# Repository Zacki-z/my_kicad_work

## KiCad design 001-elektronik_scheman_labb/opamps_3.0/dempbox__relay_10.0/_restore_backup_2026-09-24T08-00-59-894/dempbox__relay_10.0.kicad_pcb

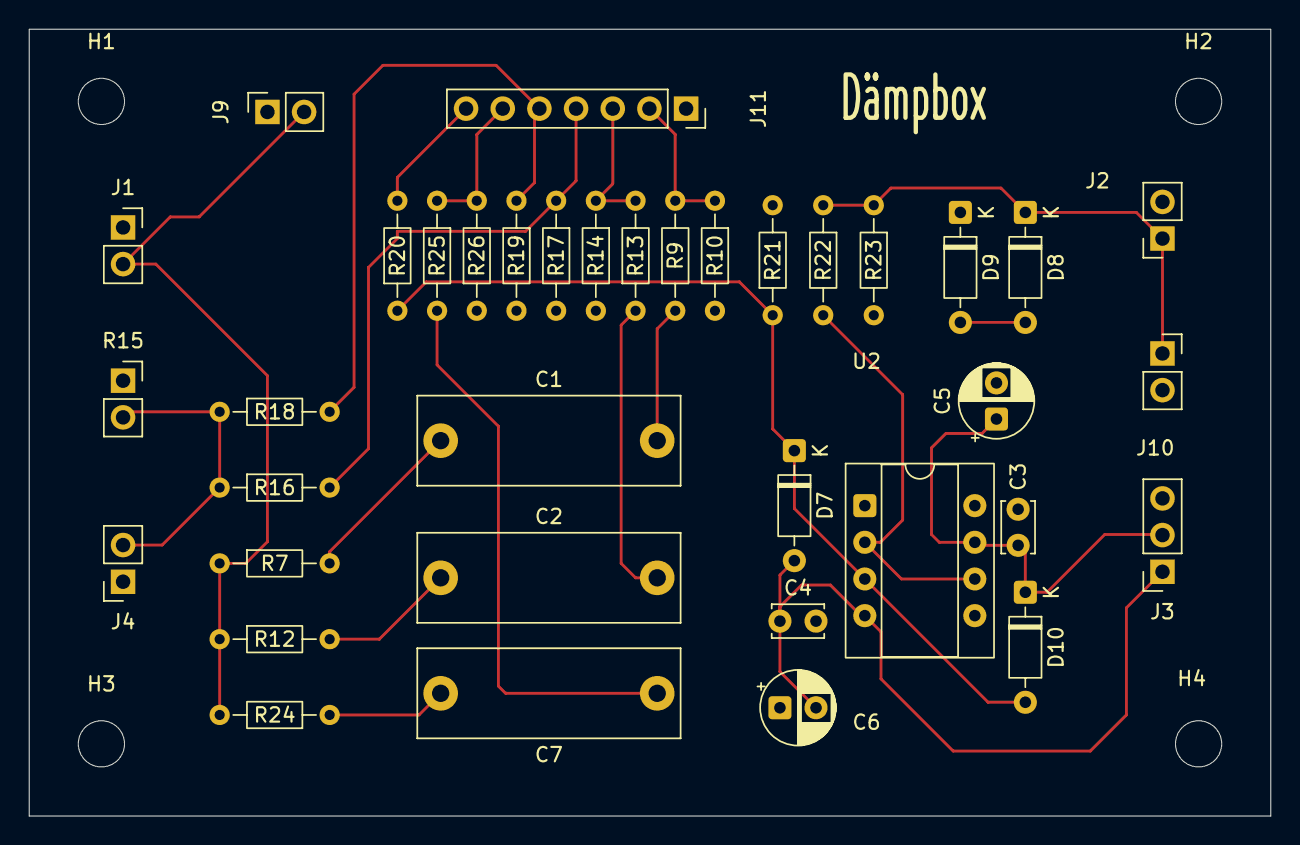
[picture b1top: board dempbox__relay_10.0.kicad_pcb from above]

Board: 2 copper layers, 86.0 x 54.5 mm, 41 parts (0 on the bottom side), 21 nets.

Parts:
C1, C2: 100 nF 630v; C_Rect_L18.0mm_W6.0mm_P15.00mm_FKS3_FKP3
C3, C4: 100 nF; C_Disc_D3.4mm_W2.1mm_P2.50mm
C5, C6: 10 uF; CP_Radial_D5.0mm_P2.50mm
C7: 100 nF 630V; C_Rect_L18.0mm_W6.0mm_P15.00mm_FKS3_FKP3
D7, D10: 1N4148; D_DO-35_SOD27_P7.62mm_Horizontal
D8, D9: BZX55C5V1; D_DO-35_SOD27_P7.62mm_Horizontal
H1, H2, H3, H4: MountingHole; MountingHole_3.2mm_M3
J1: Test_probe; PinSocket_1x02_P2.54mm_Vertical
J2: TO_Focusrite_input; PinSocket_1x02_P2.54mm_Vertical
J3: OP_AMP_PWR; PinSocket_1x03_P2.54mm_Vertical
J4: Speaker; PinSocket_1x02_P2.54mm_Vertical
J9, J10: Mätinstrument; PinSocket_1x02_P2.54mm_Vertical
J11: J_SW_SIGNAL; PinSocket_1x07_P2.54mm_Vertical
R7, R12, R21, R26: 1M; R_Axial_DIN0204_L3.6mm_D1.6mm_P7.62mm_Horizontal
R9, R13: 953k; R_Axial_DIN0204_L3.6mm_D1.6mm_P7.62mm_Horizontal
R10: 20K; R_Axial_DIN0204_L3.6mm_D1.6mm_P7.62mm_Horizontal
R14: 274k; R_Axial_DIN0204_L3.6mm_D1.6mm_P7.62mm_Horizontal
R15: 8 50W; PinSocket_1x02_P2.54mm_Vertical
R16, R23: 100k; R_Axial_DIN0204_L3.6mm_D1.6mm_P7.62mm_Horizontal
R17: 1k; R_Axial_DIN0204_L3.6mm_D1.6mm_P7.62mm_Horizontal
R18: 90,9k; R_Axial_DIN0204_L3.6mm_D1.6mm_P7.62mm_Horizontal
R19: 10k; R_Axial_DIN0204_L3.6mm_D1.6mm_P7.62mm_Horizontal
R20: 20k; R_Axial_DIN0204_L3.6mm_D1.6mm_P7.62mm_Horizontal
R22: 330R; R_Axial_DIN0204_L3.6mm_D1.6mm_P7.62mm_Horizontal
R24, R25: 10K; R_Axial_DIN0204_L3.6mm_D1.6mm_P7.62mm_Horizontal
U2: OPA134; CERDIP-8_W7.62mm_SideBrazed_Socket

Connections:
/INTPUT: J1.2, J9.2, R7.1, R12.1, R24.2
/INT_1_10: C2.1, R12.2
/INT_1_10_OUT: J11.3, R13.2, R14.1
/INT_1_100: C1.1, R7.2
/INT_1_100_OUT: J11.2, R9.2, R10.1
/LOW_1_1: C7.2, R24.1
/LOW_1_1_OUT: J11.6, R25.1, R26.2
/SPK_1_10_OUT: J11.5, R18.2, R19.1
/SPK_1_100: J4.2, R15.2, R16.1, R18.1
/SPK_1_100_OUT: J11.4, R16.2, R17.1
/sound-card/12V+: C3.1, C5.1, D10.1 (K), J3.2, U2.7 (V+)
/sound-card/12V-: C4.1, C6.2, D7.2 (A), J3.1, U2.4 (V-)
/sound-card/OP_AMP_OUT: R22.2, U2.2 (-), U2.6
/sound-card/audio_out: D8.1 (K), J2.1, J10.1, R22.1, R23.1
MEASURE_GND: C3.2, C4.2, C5.2, C6.1, D9.1 (K), J1.1, J2.2, J3.3, J4.1, J9.1, J10.2, R10.2, R14.2, R15.1, R17.2, R19.2, R21.2, R23.2, R26.1
MEASURE_SIGNAL: J11.7, R20.2
unnamed: C1.2, R9.1
unnamed: C2.2, R13.1
unnamed: C7.1, R25.2
unnamed: D8.2 (A), D9.2 (A)
unnamed: D7.1 (K), D10.2 (A), R20.1, R21.1, U2.3 (+)

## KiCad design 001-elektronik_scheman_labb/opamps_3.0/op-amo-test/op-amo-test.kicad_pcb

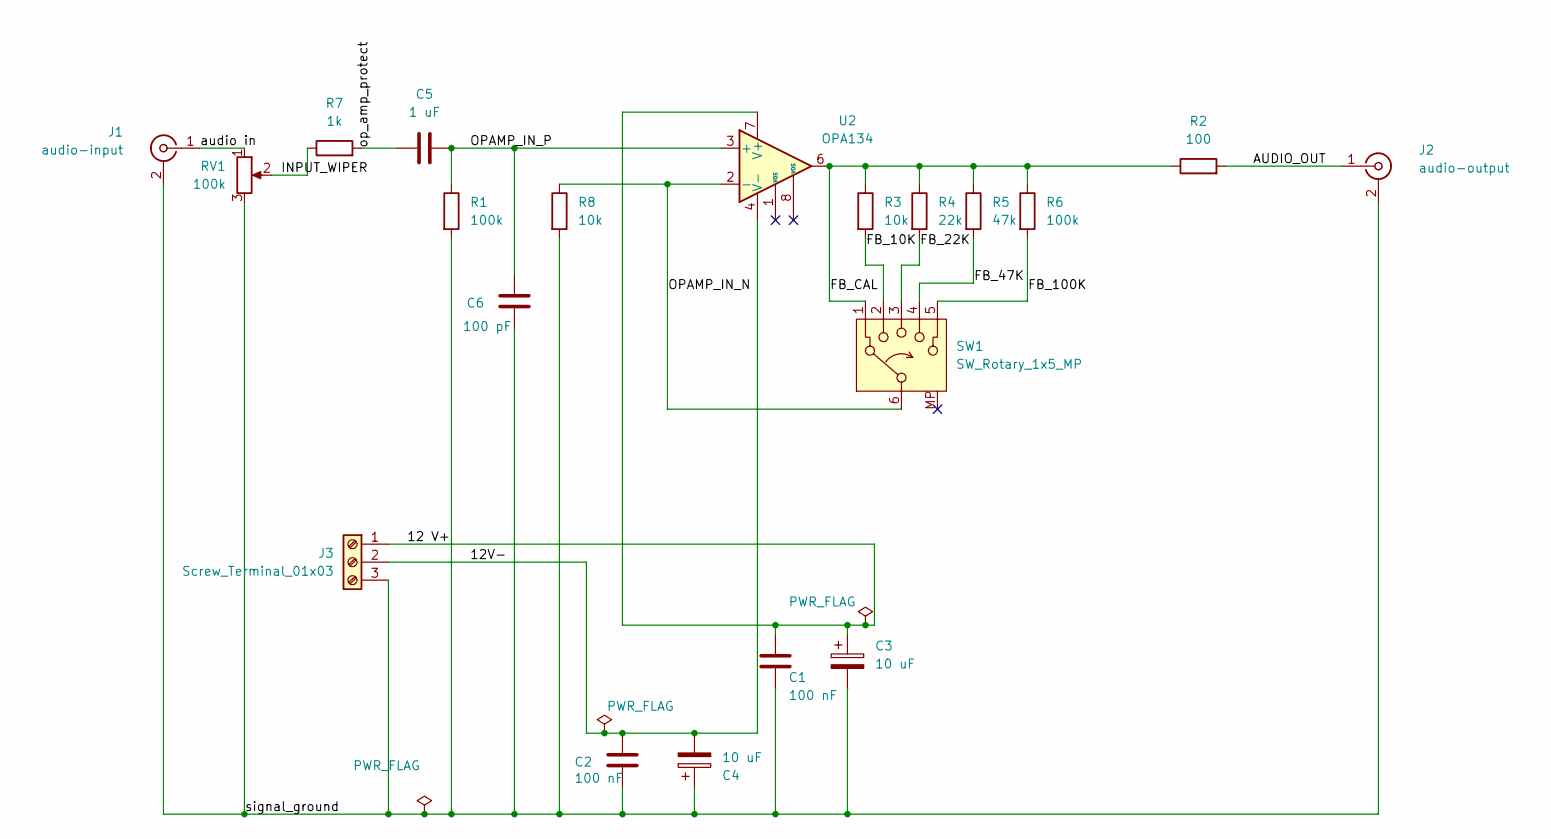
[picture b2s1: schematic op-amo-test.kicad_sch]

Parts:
C1, C2: 100 nF; C_Disc_D5.0mm_W2.5mm_P5.00mm
C3, C4: 10 uF; CP_Radial_D5.0mm_P2.00mm
C5: 1 uF; C_Axial_L12.0mm_D9.5mm_P15.00mm_Horizontal
C6: 100 pF; C_Disc_D7.5mm_W5.0mm_P5.00mm
J1: audio-input; TerminalBlock_MaiXu_MX126-5.0-02P_1x02_P5.00mm
J2: audio-output; TerminalBlock_MaiXu_MX126-5.0-02P_1x02_P5.00mm
J3: Screw_Terminal_01x03; TerminalBlock_MaiXu_MX126-5.0-03P_1x03_P5.00mm
R1, R6: 100k; R_Axial_DIN0207_L6.3mm_D2.5mm_P7.62mm_Horizontal
R2: 100; R_Axial_DIN0207_L6.3mm_D2.5mm_P7.62mm_Horizontal
R3, R8: 10k; R_Axial_DIN0207_L6.3mm_D2.5mm_P7.62mm_Horizontal
R4: 22k; R_Axial_DIN0207_L6.3mm_D2.5mm_P7.62mm_Horizontal
R5: 47k; R_Axial_DIN0207_L6.3mm_D2.5mm_P7.62mm_Horizontal
R7: 1k; R_Axial_DIN0207_L6.3mm_D2.5mm_P7.62mm_Horizontal
RV1: 100k; TerminalBlock_MaiXu_MX126-5.0-03P_1x03_P5.00mm
SW1: SW_Rotary_1x5_MP; TerminalBlock_Xinya_XY308-2.54-6P_1x06_P2.54mm_Horizontal
U2: OPA134; DIP-8_W7.62mm

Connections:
/12 V+: C1.1, C3.1, J3.1, U2.7 (V+)
/12V-: C2.1, C4.2, J3.2, U2.4 (V-)
/AUDIO_OUT: J2.1 (In), R2.2
/FB_10K: R3.2, SW1.2
/FB_22K: R4.2, SW1.3
/FB_47K: R5.2, SW1.4
/FB_100K: R6.2, SW1.5
/FB_CAL: R2.1, R3.1, R4.1, R5.1, R6.1, SW1.1, U2.6
/INPUT_WIPER: R7.1, RV1.2
/OPAMP_IN_N: R8.1, SW1.6, U2.2 (-)
/OPAMP_IN_P: C5.1, C6.1, R1.1, U2.3 (+)
/audio in: J1.1 (In), RV1.1
/op_amp_protect: C5.2, R7.2
/signal_ground: C1.2, C2.2, C3.2, C4.1, C6.2, J1.2 (Ext), J2.2 (Ext), J3.3, R1.2, R8.2, RV1.3

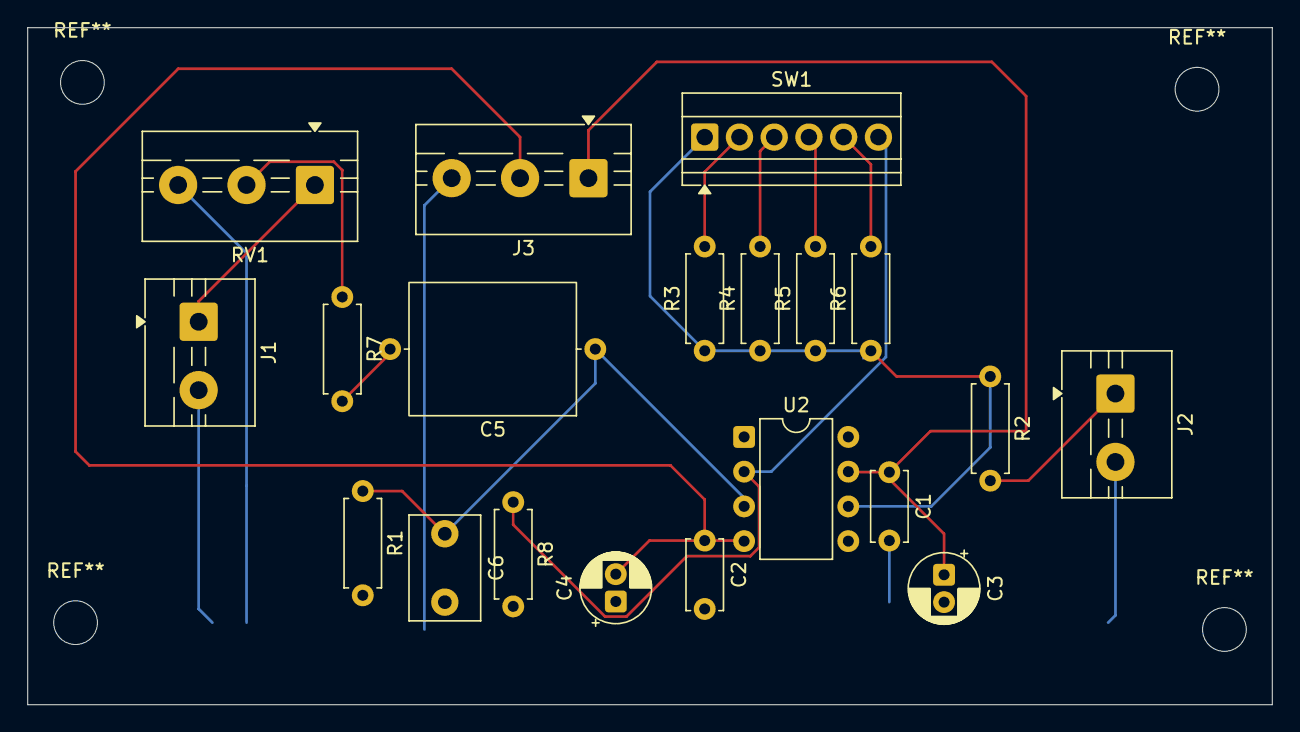
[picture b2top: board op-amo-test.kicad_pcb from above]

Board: 2 copper layers, 91.0 x 49.5 mm, 20 parts (0 on the bottom side), 14 nets.

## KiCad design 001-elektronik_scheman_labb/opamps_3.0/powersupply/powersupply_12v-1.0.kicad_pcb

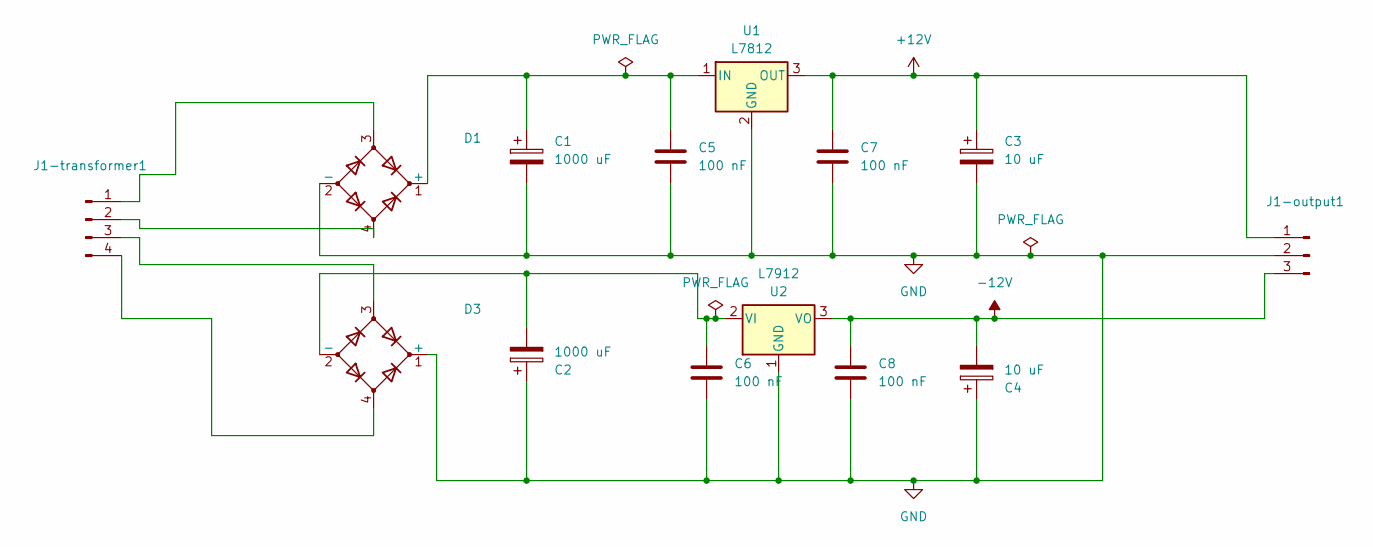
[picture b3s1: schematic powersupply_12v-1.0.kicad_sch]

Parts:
C1, C2: 1000 uF; CP_Radial_D16.0mm_P7.50mm
C3, C4: 10 uF; CP_Radial_D5.0mm_P2.50mm
C5, C6, C7, C8: 100 nF; C_Disc_D3.8mm_W2.6mm_P2.50mm
D1, D3: D_Bridge_+-AA; Diode_Bridge_Round_D8.9mm
J1-output1: Conn_01x03_Pin; PinHeader_1x03_P2.54mm_Vertical
J1-transformer1: Conn_01x04_Pin; PinHeader_1x04_P2.54mm_Vertical
U1: L7812; TO-220-3_Vertical
U2: L7912; TO-220-3_Vertical

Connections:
+12V: C3.1, C7.1, J1-output1.1, U1.3 (OUT)
-12V: C4.2, C8.1, J1-output1.3, U2.3 (VO)
GND: C1.2, C2.1, C3.2, C4.1, C5.2, C6.2, C7.2, C8.2, D1.2 (-), D3.1 (+), J1-output1.2, U1.2 (GND), U2.1 (GND)
unnamed: C1.1, C5.1, D1.1 (+), U1.1 (IN)
unnamed: C2.2, C6.1, D3.2 (-), U2.2 (VI)
unnamed: D1.3, J1-transformer1.1
unnamed: D1.4, J1-transformer1.2
unnamed: D3.3, J1-transformer1.3
unnamed: D3.4, J1-transformer1.4

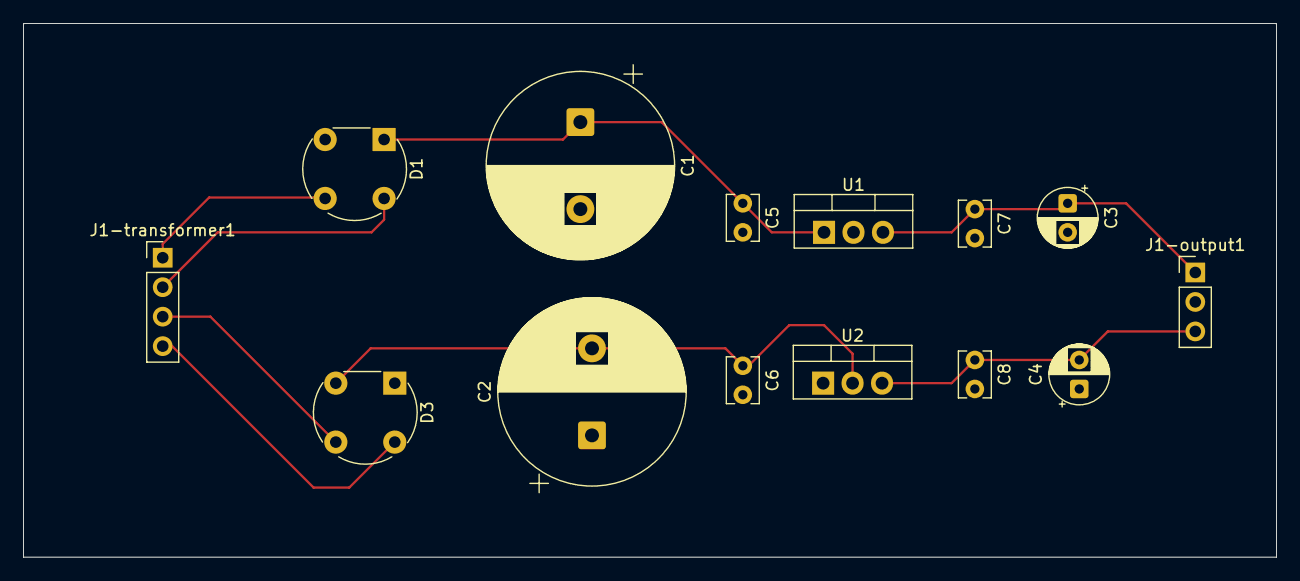
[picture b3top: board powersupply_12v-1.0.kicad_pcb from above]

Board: 2 copper layers, 108.0 x 46.0 mm, 14 parts (0 on the bottom side), 9 nets.
